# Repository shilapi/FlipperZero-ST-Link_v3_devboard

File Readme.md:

# Flipper Zero ST-Link 3.0 devkit

Converted from [flipperzero-devboard-stlinkv3](https://github.com/flipperdevices/flipperzero-devboard-stlinkv3)

Edited by Shilapi

## KiCad

## JLC

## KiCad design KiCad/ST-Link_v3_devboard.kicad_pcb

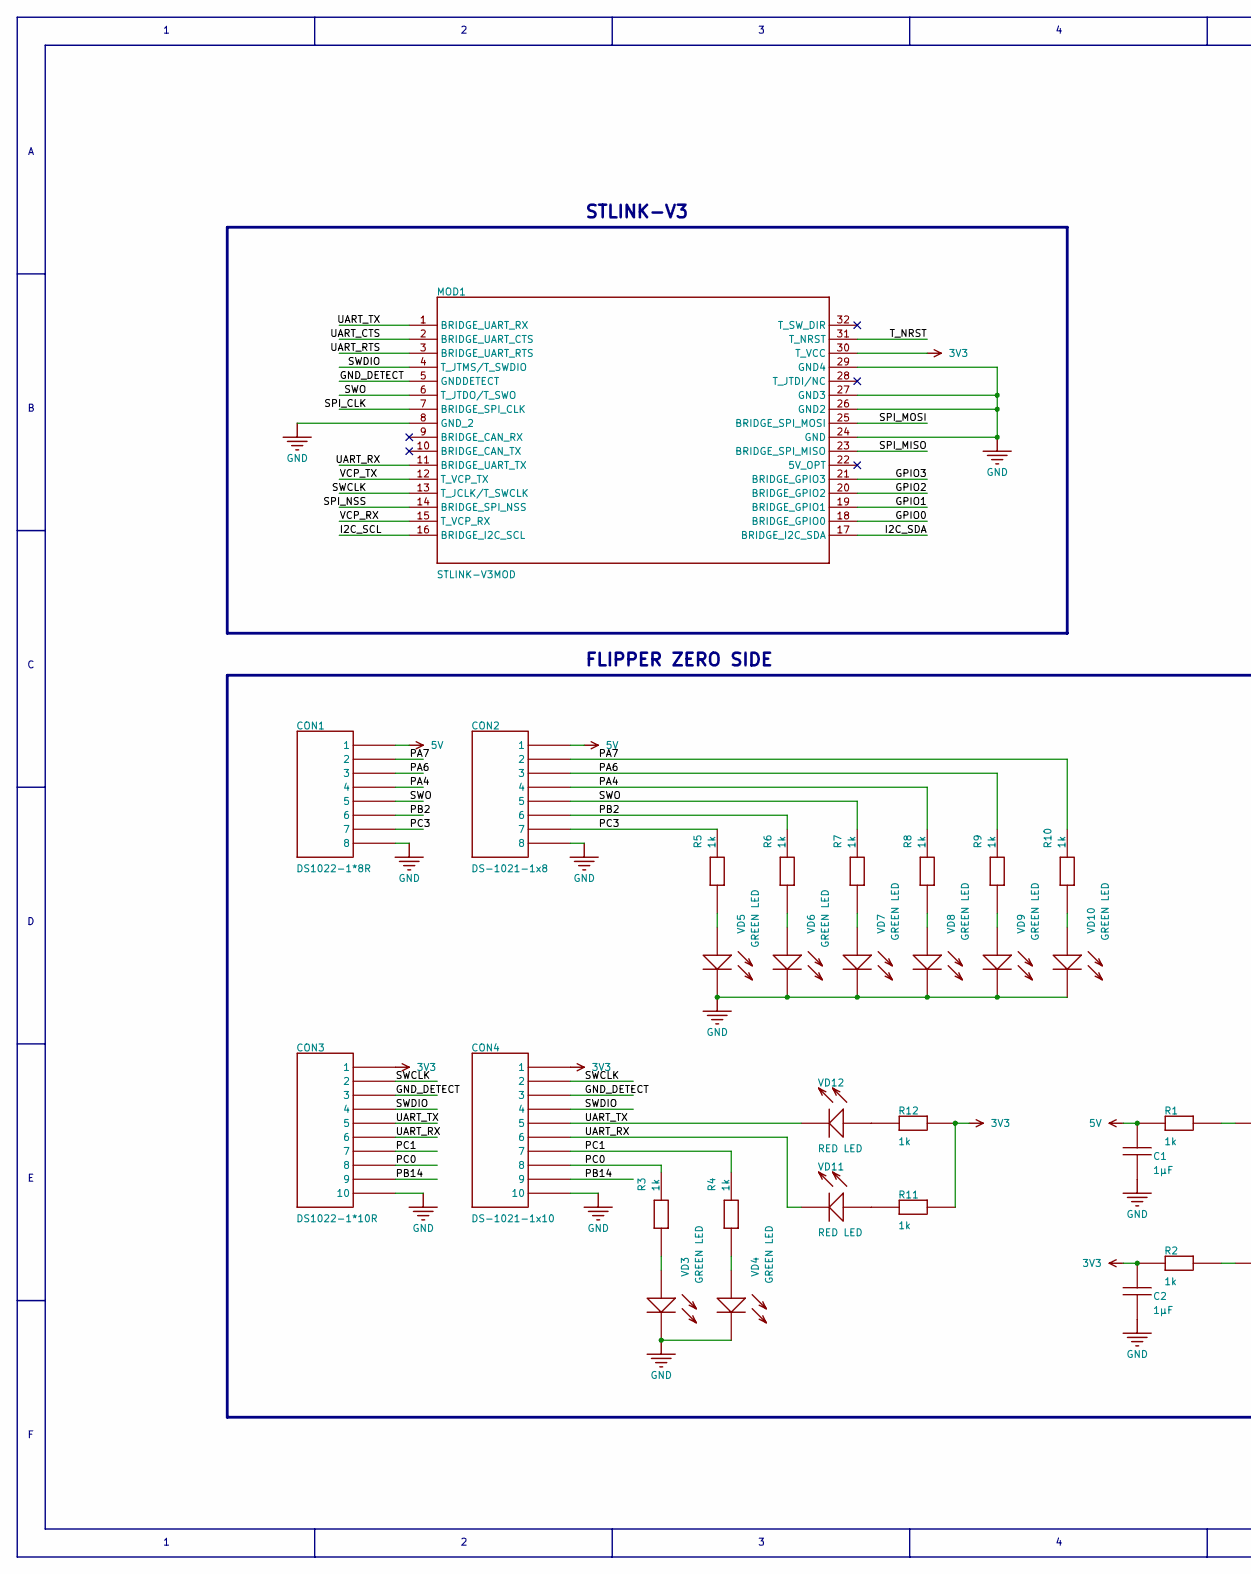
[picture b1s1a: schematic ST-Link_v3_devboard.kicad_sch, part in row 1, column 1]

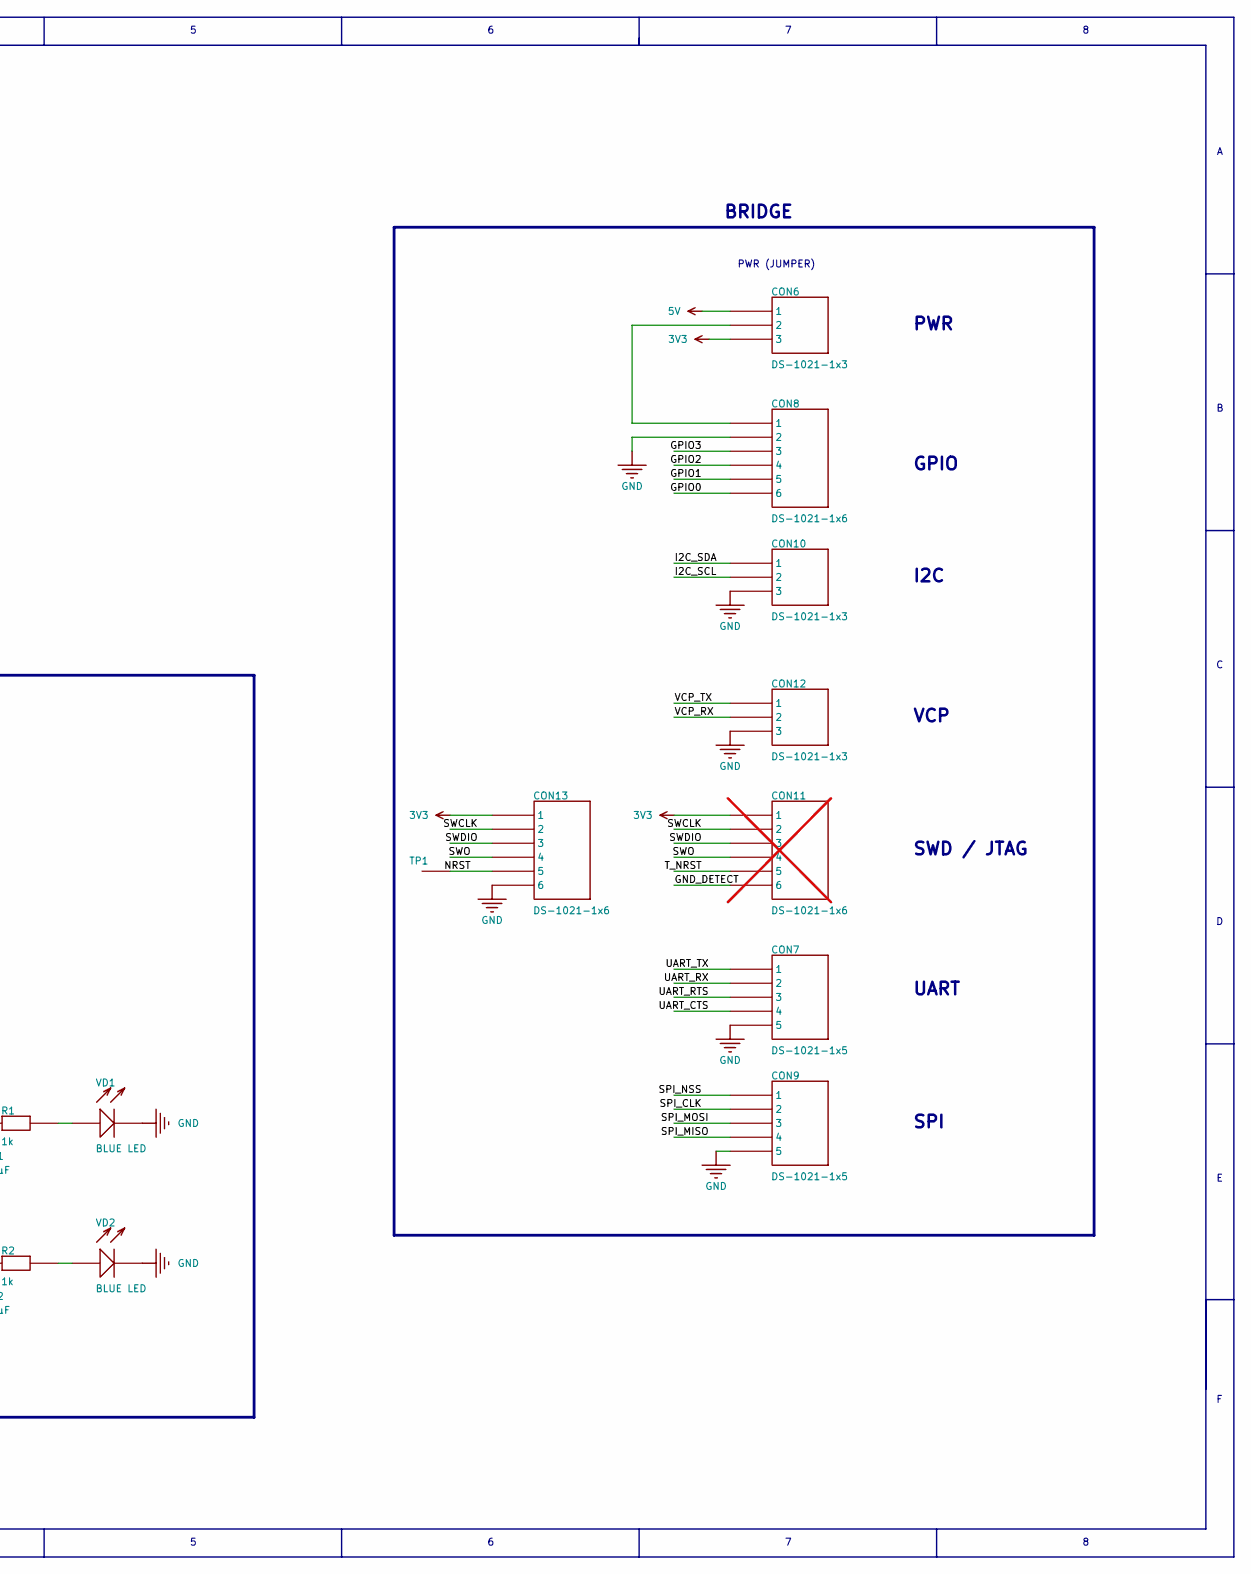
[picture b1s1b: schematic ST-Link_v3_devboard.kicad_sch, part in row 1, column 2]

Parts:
C1, C2: 1uF; C_0603_1608Metric; TOLERANCE 10%; VOLTAGE 16V
CON1: DS1022-1*8R; PinHeader_1x08_P2.54mm_Horizontal
CON2: DS-1021-1x8; PinHeader_1x08_P2.54mm_Vertical
CON3: DS1022-1*10R; PinHeader_1x10_P2.54mm_Horizontal
CON4: DS-1021-1x10; PinHeader_1x10_P2.54mm_Vertical
CON6, CON10, CON12: DS-1021-1x3; PinHeader_1x03_P2.54mm_Vertical
CON7, CON9: DS-1021-1x5; PinHeader_1x05_P2.54mm_Vertical
CON8, CON13: DS-1021-1x6; PinHeader_1x06_P2.54mm_Vertical
CON11: DS-1021-1x6; PinHeader_1x06_P2.54mm_Vertical; not fitted
MOD1: STLINK-V3MOD; MODULE_STLINK-V3MODS
R1, R2, R3, R4, R5, R6, R7, R8, R9, R10, R11, R12: 1K; R_0603_1608Metric; VOLTAGE RATING 50V; TOLERANCE 5%
TP1: Control_point; TestPoint_Pad_D1.0mm
VD1, VD2: BLUE LED; LED_0603_1608Metric
VD3, VD4, VD5, VD6, VD7, VD8, VD9, VD10: GREEN LED; LED_0603_1608Metric
VD11, VD12: RED LED; LED_0603_1608Metric

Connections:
3V3: C2.2, CON3.1, CON4.1, CON6.3, CON11.1, CON13.1, MOD1.30 (T_VCC), R2.1, R11.2, R12.2
5V: C1.2, CON1.1, CON2.1, CON6.1, R1.1
/GND_DETECT: CON3.3, CON4.3, CON11.6, MOD1.5 (GNDDETECT)
/GPIO0: CON8.6, MOD1.18 (BRIDGE_GPIO0)
/GPIO1: CON8.5, MOD1.19 (BRIDGE_GPIO1)
/GPIO2: CON8.4, MOD1.20 (BRIDGE_GPIO2)
/GPIO3: CON8.3, MOD1.21 (BRIDGE_GPIO3)
/I2C_SCL: CON10.2, MOD1.16 (BRIDGE_I2C_SCL)
/I2C_SDA: CON10.1, MOD1.17 (BRIDGE_I2C_SDA)
/NRST: CON13.5, TP1.1
/PA4: CON1.4, CON2.4, R8.2
/PA6: CON1.3, CON2.3, R9.2
/PA7: CON1.2, CON2.2, R10.2
/PB2: CON1.6, CON2.6, R6.2
/PB14: CON3.9, CON4.9
/PC0: CON3.8, CON4.8, R3.2
/PC1: CON3.7, CON4.7, R4.2
/PC3: CON1.7, CON2.7, R5.2
/SPI_CLK: CON9.2, MOD1.7 (BRIDGE_SPI_CLK)
/SPI_MISO: CON9.4, MOD1.23 (BRIDGE_SPI_MISO)
/SPI_MOSI: CON9.3, MOD1.25 (BRIDGE_SPI_MOSI)
/SPI_NSS: CON9.1, MOD1.14 (BRIDGE_SPI_NSS)
/SWCLK: CON3.2, CON4.2, CON11.2, CON13.2, MOD1.13 (T_JCLK/T_SWCLK)
/SWDIO: CON3.4, CON4.4, CON11.3, CON13.3, MOD1.4 (T_JTMS/T_SWDIO)
/SWO: CON1.5, CON2.5, CON11.4, CON13.4, MOD1.6 (T_JTDO/T_SWO), R7.2
/T_NRST: CON11.5, MOD1.31 (T_NRST)
/UART_CTS: CON7.4, MOD1.2 (BRIDGE_UART_CTS)
/UART_RTS: CON7.3, MOD1.3 (BRIDGE_UART_RTS)
/UART_RX: CON3.6, CON4.6, CON7.2, MOD1.11 (BRIDGE_UART_TX), VD11.1
/UART_TX: CON3.5, CON4.5, CON7.1, MOD1.1 (BRIDGE_UART_RX), VD12.1
/VCP_RX: CON12.2, MOD1.15 (T_VCP_RX)
/VCP_TX: CON12.1, MOD1.12 (T_VCP_TX)
GND: C1.1, C2.1, CON1.8, CON2.8, CON3.10, CON4.10, CON7.5, CON8.2, CON9.5, CON10.3, CON12.3, CON13.6, MOD1.8 (GND_2), MOD1.24 (GND), MOD1.26 (GND2), MOD1.27 (GND3), MOD1.29 (GND4), VD1.1, VD2.1, VD3.1, VD4.1, VD5.1, VD6.1, VD7.1, VD8.1, VD9.1, VD10.1
unnamed: CON6.2, CON8.1
unnamed: R1.2, VD1.2
unnamed: R2.2, VD2.2
unnamed: R3.1, VD3.2
unnamed: R4.1, VD4.2
unnamed: R5.1, VD5.2
unnamed: R6.1, VD6.2
unnamed: R7.1, VD7.2
unnamed: R8.1, VD8.2
unnamed: R9.1, VD9.2
unnamed: R10.1, VD10.2
unnamed: R11.1, VD11.2
unnamed: R12.1, VD12.2

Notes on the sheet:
UART
FLIPPER ZERO SIDE
BRIDGE
PWR
STLINK-V3
I2C
VCP
SPI
SWD / JTAG
PWR (JUMPER)
GPIO

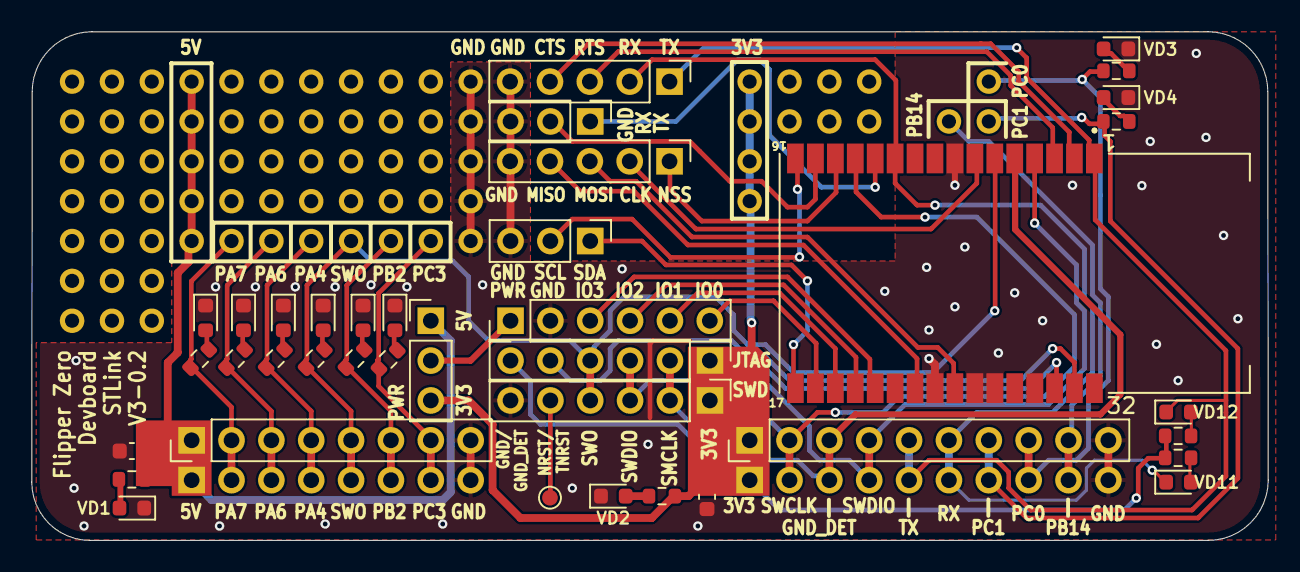
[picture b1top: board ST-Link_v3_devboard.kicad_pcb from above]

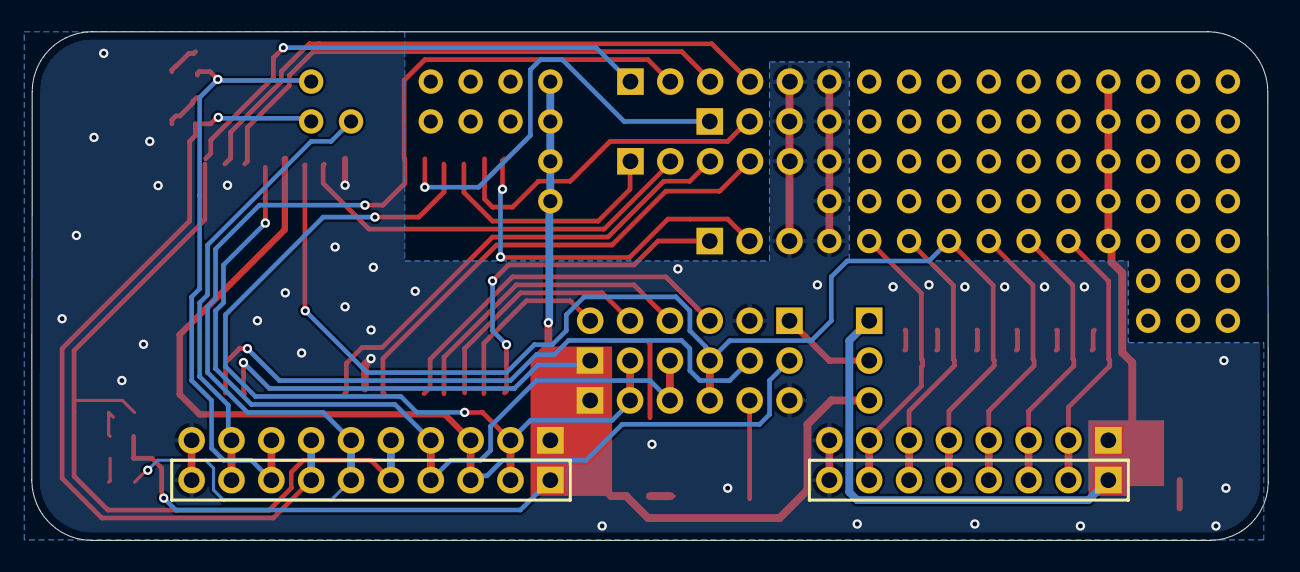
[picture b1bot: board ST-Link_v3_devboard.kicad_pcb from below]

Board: 2 copper layers, 78.8 x 32.4 mm, 40 parts (2 on the bottom side), 46 nets.

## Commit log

2024-10-15 Init with all files
